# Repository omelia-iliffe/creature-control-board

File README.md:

# SECOND RELEASE COMING SOON
Open an issue to request features!

I am developing a circuit board for non-organic creatures.

#### Useful links:
Auto-Program circuit - https://arduino.stackexchange.com/questions/38012/major-difference-between-dtr-signal-and-rts-signal

| GPIO Determining the Boot Mode |           |          |               |
|--------------------------------|-----------|----------|---------------|
| Pin                            | Default   | Run Mode | Download Mode |
| IO0                            | Pull-up   | 1        | 0             |
| TXD0                           | Pull-up   | 1        | x             |
| IO2                            | Pull-down | x        | 0             |
| IO5                            | Pull-up   | 1        | x             |
(Table from https://www.sparkfun.com/news/2017)

Breakout Board for LSM6DS3 - https://github.com/sparkfun/LSM6DS3_Breakout
https://learn.sparkfun.com/tutorials/lsm6ds3-breakout-hookup-guide

Breakout Board for TPA2005D1 - https://github.com/sparkfun/Mono_Audio_Amp_Breakout-TPA2005D1
http://cdn.sparkfun.com/datasheets/BreakoutBoards/Mono%20Audio%20Amp%20TPA2005D1%20v10.pdf

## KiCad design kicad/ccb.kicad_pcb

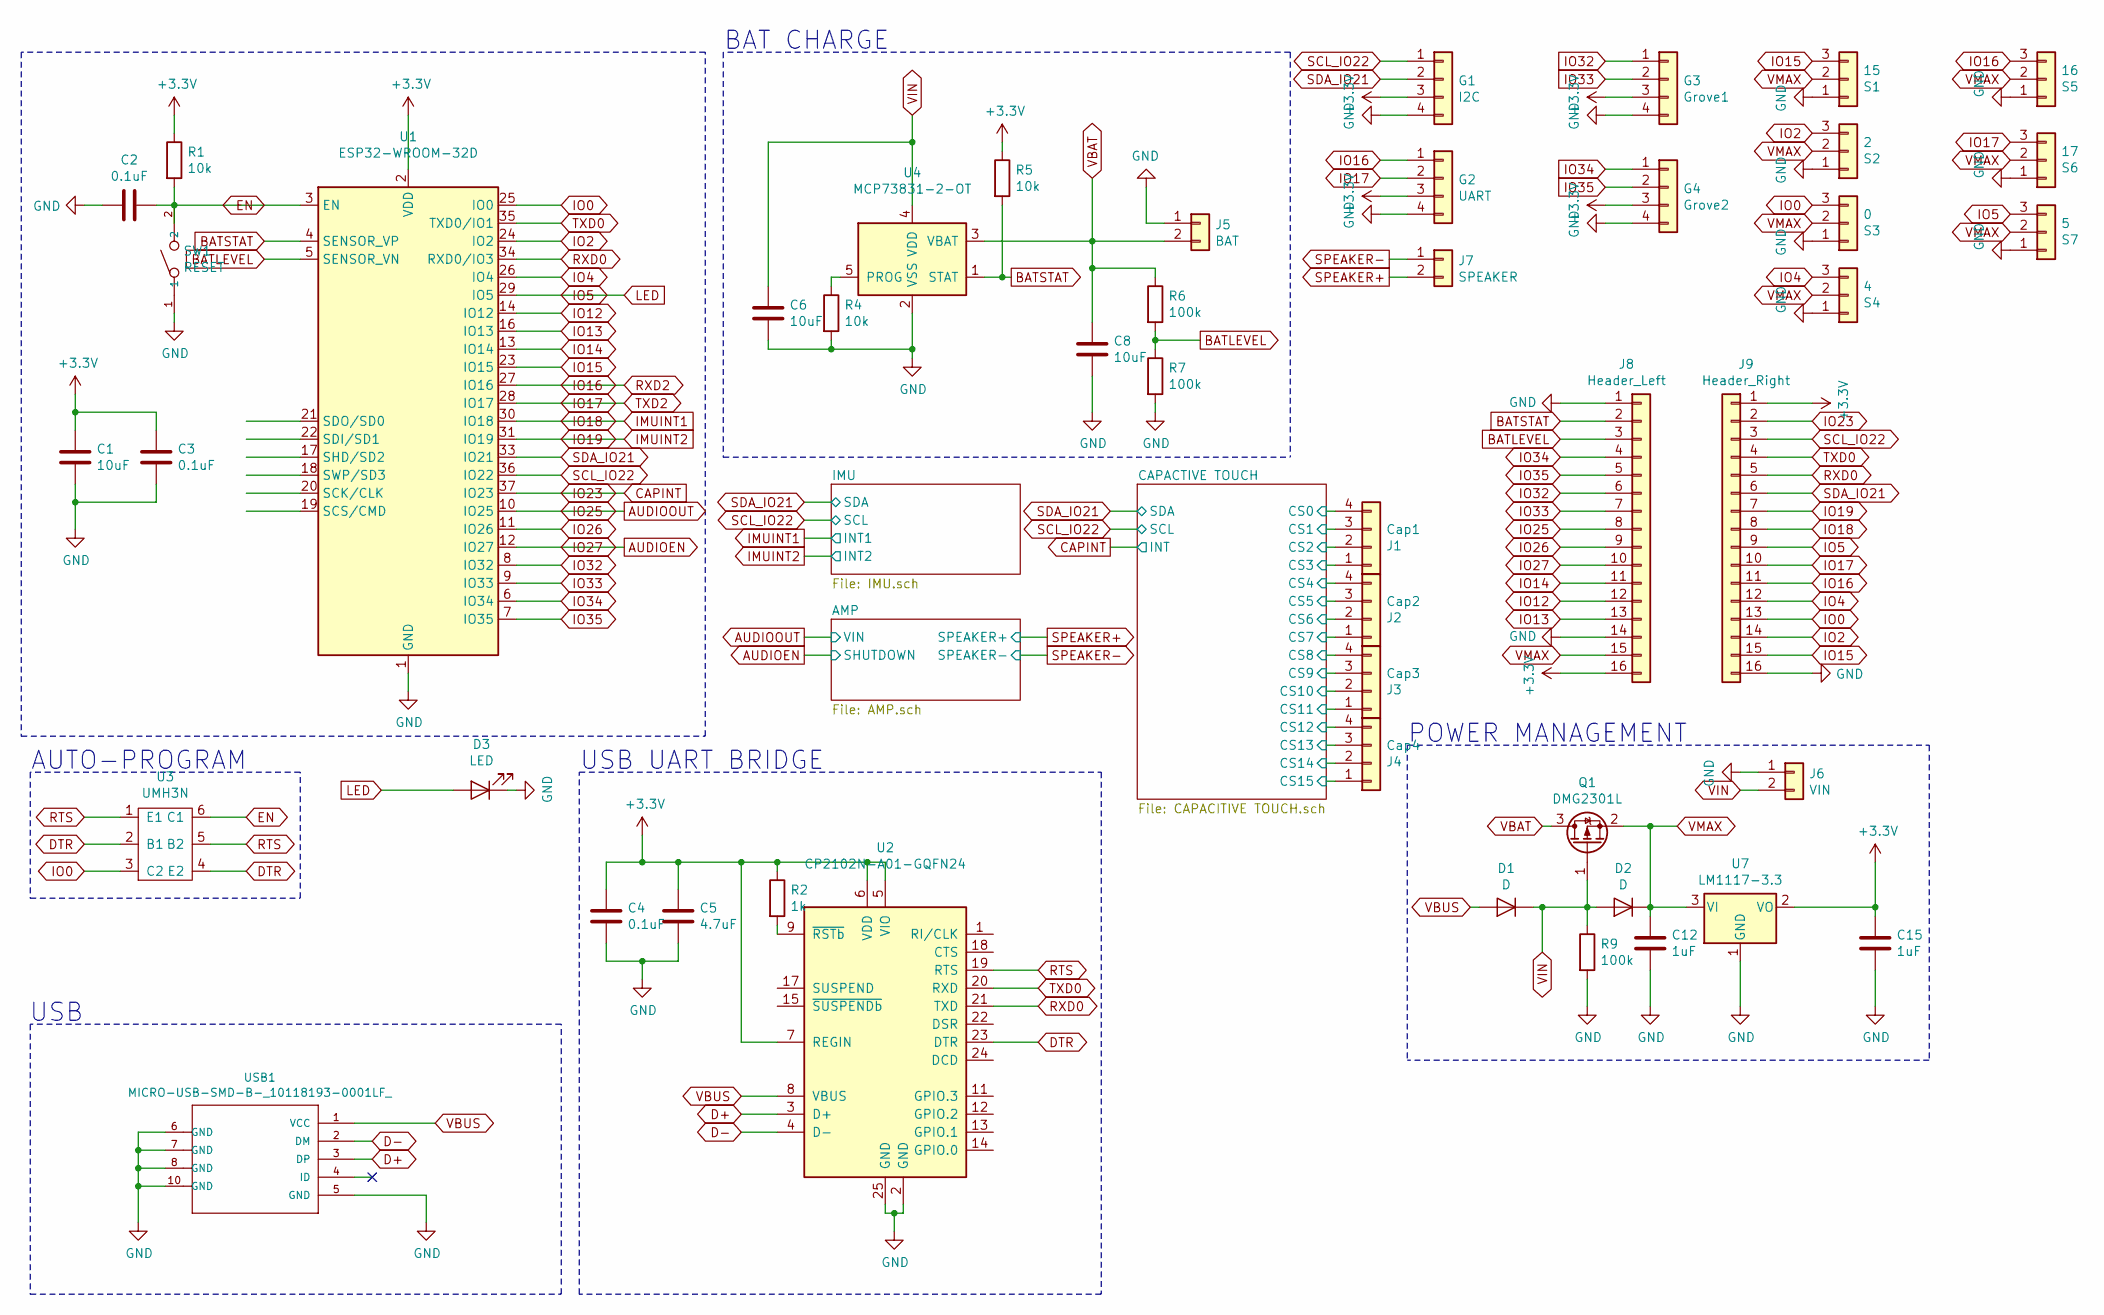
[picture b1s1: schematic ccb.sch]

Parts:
C1, C6, C8: 10uF; C_0805_2012Metric; MPN CL21A106KPFNNNE
C2, C3, C4: 0.1uF; C_0805_2012Metric; MPN CL21B104MACNNNC
C5: 4.7uF; C_0805_2012Metric; MPN CL21A475KPFNNNG
C12, C15: 1uF; C_0805_2012Metric; MPN CL21B105KOFNNNG
D1, D2: D; D_SOD-323; MPN BAT60JFILM
D3: LED; LED_1206_3216Metric_Pad1.42x1.75mm_HandSolder
G1: I2C; NS-Tech_Grove_1x04_P2mm_Vertical; MPN 110990030
G2: UART; NS-Tech_Grove_1x04_P2mm_Vertical; MPN 110990030
G3: Grove1; NS-Tech_Grove_1x04_P2mm_Vertical; MPN 110990030
G4: Grove2; NS-Tech_Grove_1x04_P2mm_Vertical; MPN 110990030
J1: Cap1; JST_PH_S4B-PH-K_1x04_P2.00mm_Horizontal; MPN S4B-PH-K-S(LF)(SN)
J2: Cap2; JST_PH_S4B-PH-K_1x04_P2.00mm_Horizontal; MPN S4B-PH-K-S(LF)(SN)
J3: Cap3; JST_PH_S4B-PH-K_1x04_P2.00mm_Horizontal; MPN S4B-PH-K-S(LF)(SN)
J4: Cap4; JST_PH_S4B-PH-K_1x04_P2.00mm_Horizontal; MPN S4B-PH-K-S(LF)(SN)
J5: BAT; JST_PH_S2B-PH-K_1x02_P2.00mm_Horizontal; MPN S2B-PH-K-S(LF)(SN)
J6: VIN; JST_PH_S2B-PH-K_1x02_P2.00mm_Horizontal; MPN S2B-PH-K-S(LF)(SN)
J7: SPEAKER; JST_PH_S2B-PH-K_1x02_P2.00mm_Horizontal; MPN S2B-PH-K-S(LF)(SN)
J8: Header_Left; PinSocket_1x16_P2.54mm_Vertical; MPN 0022032161
J9: Header_Right; PinSocket_1x16_P2.54mm_Vertical; MPN 0022032161
Q1: DMG2301L; SOT-23; MPN NTR3A052PZT1G
R1, R4, R5: 10k; R_0805_2012Metric; MPN RMCF0805FT10K0
R2: 1k; R_0805_2012Metric; MPN RMCF0805FT1K00
R6, R7, R9: 100k; R_0805_2012Metric; MPN RMCF0805FT100K
S1: 15; PinHeader_1x03_P2.54mm_Vertical; MPN WM4001-ND
S2: 2; PinHeader_1x03_P2.54mm_Vertical; MPN WM4001-ND
S3: 0; PinHeader_1x03_P2.54mm_Vertical; MPN WM4001-ND
S4: 4; PinHeader_1x03_P2.54mm_Vertical; MPN WM4001-ND
S5: 16; PinHeader_1x03_P2.54mm_Vertical; MPN WM4001-ND
S6: 17; PinHeader_1x03_P2.54mm_Vertical; MPN WM4001-ND
S7: 5; PinHeader_1x03_P2.54mm_Vertical; MPN WM4001-ND
SW1: RESET; SW2-2.6-3.0X2.5X1.2+0.4MM; MPN B3U-1000P
U1: ESP32-WROOM-32D; ESP32-WROOM-32; MPN ESP32-WROOM-32D
U2: CP2102N-A01-GQFN24; QFN-24-1EP_4x4mm_P0.5mm_EP2.6x2.6mm; MPN CP2102N-A02-GQFN24R
U3: UMH3N; MPN UMH3NTN
U4: MCP73831-2-OT; SOT-23-5; MPN MCP73831T-2ACI/OT
U7: LM1117-3.3; TO-252; MPN LM1117IMPX-3.3/NOPB
USB1: MICRO-USB-SMD-B-_10118193-0001LF_; MICRO-USB5+6P-SMD-0.65-B; MPN 10118193-0001LF

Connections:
+3V3: C1.2, C3.2, C4.2, C5.2, C15.2, G1.3, G2.3, G3.3, G4.3, J8.16, J9.1, R1.1, R2.1, R5.1, U1.2 (VDD), U2.5 (VIO), U2.6 (VDD), U2.7 (REGIN), U7.2 (VO); also elsewhere on the board
/CAPACTIVE TOUCH/CS0: J1.4; also elsewhere on the board
/CAPACTIVE TOUCH/CS1: J1.3; also elsewhere on the board
/CAPACTIVE TOUCH/CS2: J1.2; also elsewhere on the board
/CAPACTIVE TOUCH/CS3: J1.1; also elsewhere on the board
/CAPACTIVE TOUCH/CS4: J2.4; also elsewhere on the board
/CAPACTIVE TOUCH/CS5: J2.3; also elsewhere on the board
/CAPACTIVE TOUCH/CS6: J2.2; also elsewhere on the board
/CAPACTIVE TOUCH/CS7: J2.1; also elsewhere on the board
/CAPACTIVE TOUCH/CS8: J3.4; also elsewhere on the board
/CAPACTIVE TOUCH/CS9: J3.3; also elsewhere on the board
/CAPACTIVE TOUCH/CS10: J3.2; also elsewhere on the board
/CAPACTIVE TOUCH/CS11: J3.1; also elsewhere on the board
/CAPACTIVE TOUCH/CS12: J4.4; also elsewhere on the board
/CAPACTIVE TOUCH/CS13: J4.3; also elsewhere on the board
/CAPACTIVE TOUCH/CS14: J4.2; also elsewhere on the board
/CAPACTIVE TOUCH/CS15: J4.1; also elsewhere on the board
AUDIOEN: J8.10, U1.12 (IO27); also elsewhere on the board
AUDIOOUT: J8.8, U1.10 (IO25); also elsewhere on the board
BATLEVEL: J8.3, R6.2, R7.1, U1.5 (SENSOR_VN)
BATSTAT: J8.2, R5.2, U1.4 (SENSOR_VP), U4.1 (STAT)
CAPINT: J9.2, U1.37 (IO23); also elsewhere on the board
D+: U2.3 (D+), USB1.3 (DP)
D-: U2.4 (D-), USB1.2 (DM)
DTR: U2.23 (DTR), U3.2 (B1), U3.4 (E2)
EN: C2.1, R1.2, SW1.2, U1.3 (EN), U3.6 (C1)
GND: C1.1, C2.2, C3.1, C4.1, C5.1, C6.1, C8.1, C12.1, C15.1, D3.1 (K), G1.4, G2.4, G3.4, G4.4, J5.1, J6.1, J8.1, J8.14, J9.16, R4.2, R7.2, R9.2, S1.1, S2.1, S3.1, S4.1, S5.1, S6.1, S7.1, SW1.1, U1.1 (GND), U1.15 (GND), U1.38 (GND), U2.2 (GND), U2.25 (GND), U4.2 (VSS), U7.1 (GND), USB1.5 (GND), USB1.6 (GND), USB1.7 (GND), USB1.8 (GND), USB1.9 (GND), USB1.10 (GND), USB1.11 (GND); also elsewhere on the board
IMUINT1: J9.8, U1.30 (IO18); also elsewhere on the board
IMUINT2: J9.7, U1.31 (IO19); also elsewhere on the board
IO0: J9.13, S3.3, U1.25 (IO0), U3.3 (C2)
IO2: J9.14, S2.3, U1.24 (IO2)
IO4: J9.12, S4.3, U1.26 (IO4)
IO5: D3.2 (A), J9.9, S7.3, U1.29 (IO5)
IO12: J8.12, U1.14 (IO12)
IO13: J8.13, U1.16 (IO13)
IO14: J8.11, U1.13 (IO14)
IO15: J9.15, S1.3, U1.23 (IO15)
IO16: G2.1, J9.11, S5.3, U1.27 (IO16)
IO17: G2.2, J9.10, S6.3, U1.28 (IO17)
IO26: J8.9, U1.11 (IO26)
IO32: G3.1, J8.6, U1.8 (IO32)
IO33: G3.2, J8.7, U1.9 (IO33)
IO34: G4.1, J8.4, U1.6 (IO34)
IO35: G4.2, J8.5, U1.7 (IO35)
unnamed: R2.2, U2.9 (~RSTb)
unnamed: R4.1, U4.5 (PROG)
RTS: U2.19 (RTS), U3.1 (E1), U3.5 (B2)
RXD0: J9.5, U1.34 (RXD0/IO3), U2.21 (TXD)
SCL_IO22: G1.1, J9.3, U1.36 (IO22); also elsewhere on the board
SDA_IO21: G1.2, J9.6, U1.33 (IO21); also elsewhere on the board
SPEAKER+: J7.2; also elsewhere on the board
SPEAKER-: J7.1; also elsewhere on the board
TXD0: J9.4, U1.35 (TXD0/IO1), U2.20 (RXD)
VBAT: C8.2, J5.2, Q1.3 (D), R6.1, U4.3 (VBAT)
VBUS: D1.2 (A), U2.8 (VBUS), USB1.1 (VCC)
VIN: C6.2, D1.1 (K), D2.2 (A), J6.2, Q1.1 (G), R9.1, U4.4 (VDD)
VMAX: C12.2, D2.1 (K), J8.15, Q1.2 (S), S1.2, S2.2, S3.2, S4.2, S5.2, S6.2, S7.2, U7.3 (VI)

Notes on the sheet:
USB
USB UART BRIDGE
AUTO-PROGRAM
BAT CHARGE
POWER MANAGEMENT

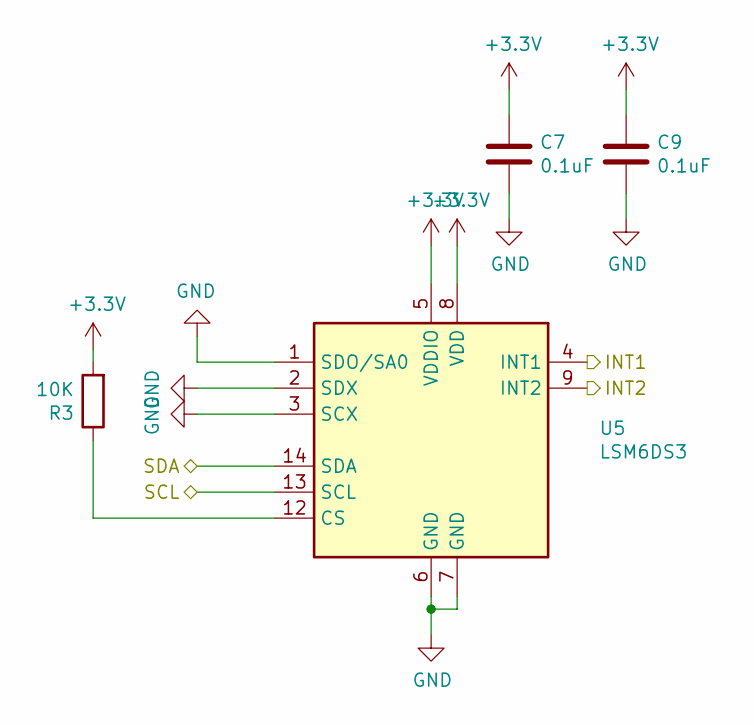
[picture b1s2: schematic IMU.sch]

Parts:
C7, C9: 0.1uF; C_0805_2012Metric; MPN CL21B104MACNNNC
R3: 10K; R_0805_2012Metric; MPN RMCF0805FT10K0
U5: LSM6DS3; LGA-14L_2.5x3mm__LSM6DS3; MPN LSM6DS3TR

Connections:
+3V3: C7.2, C9.2, R3.2, U5.5 (VDDIO), U5.8 (VDD); also elsewhere on the board
GND: C7.1, C9.1, U5.1 (SDO/SA0), U5.2 (SDX), U5.3 (SCX), U5.6 (GND), U5.7 (GND); also elsewhere on the board
IMUINT1: U5.4 (INT1); also elsewhere on the board
IMUINT2: U5.9 (INT2); also elsewhere on the board
unnamed: R3.1, U5.12 (CS)
SCL_IO22: U5.13 (SCL); also elsewhere on the board
SDA_IO21: U5.14 (SDA); also elsewhere on the board

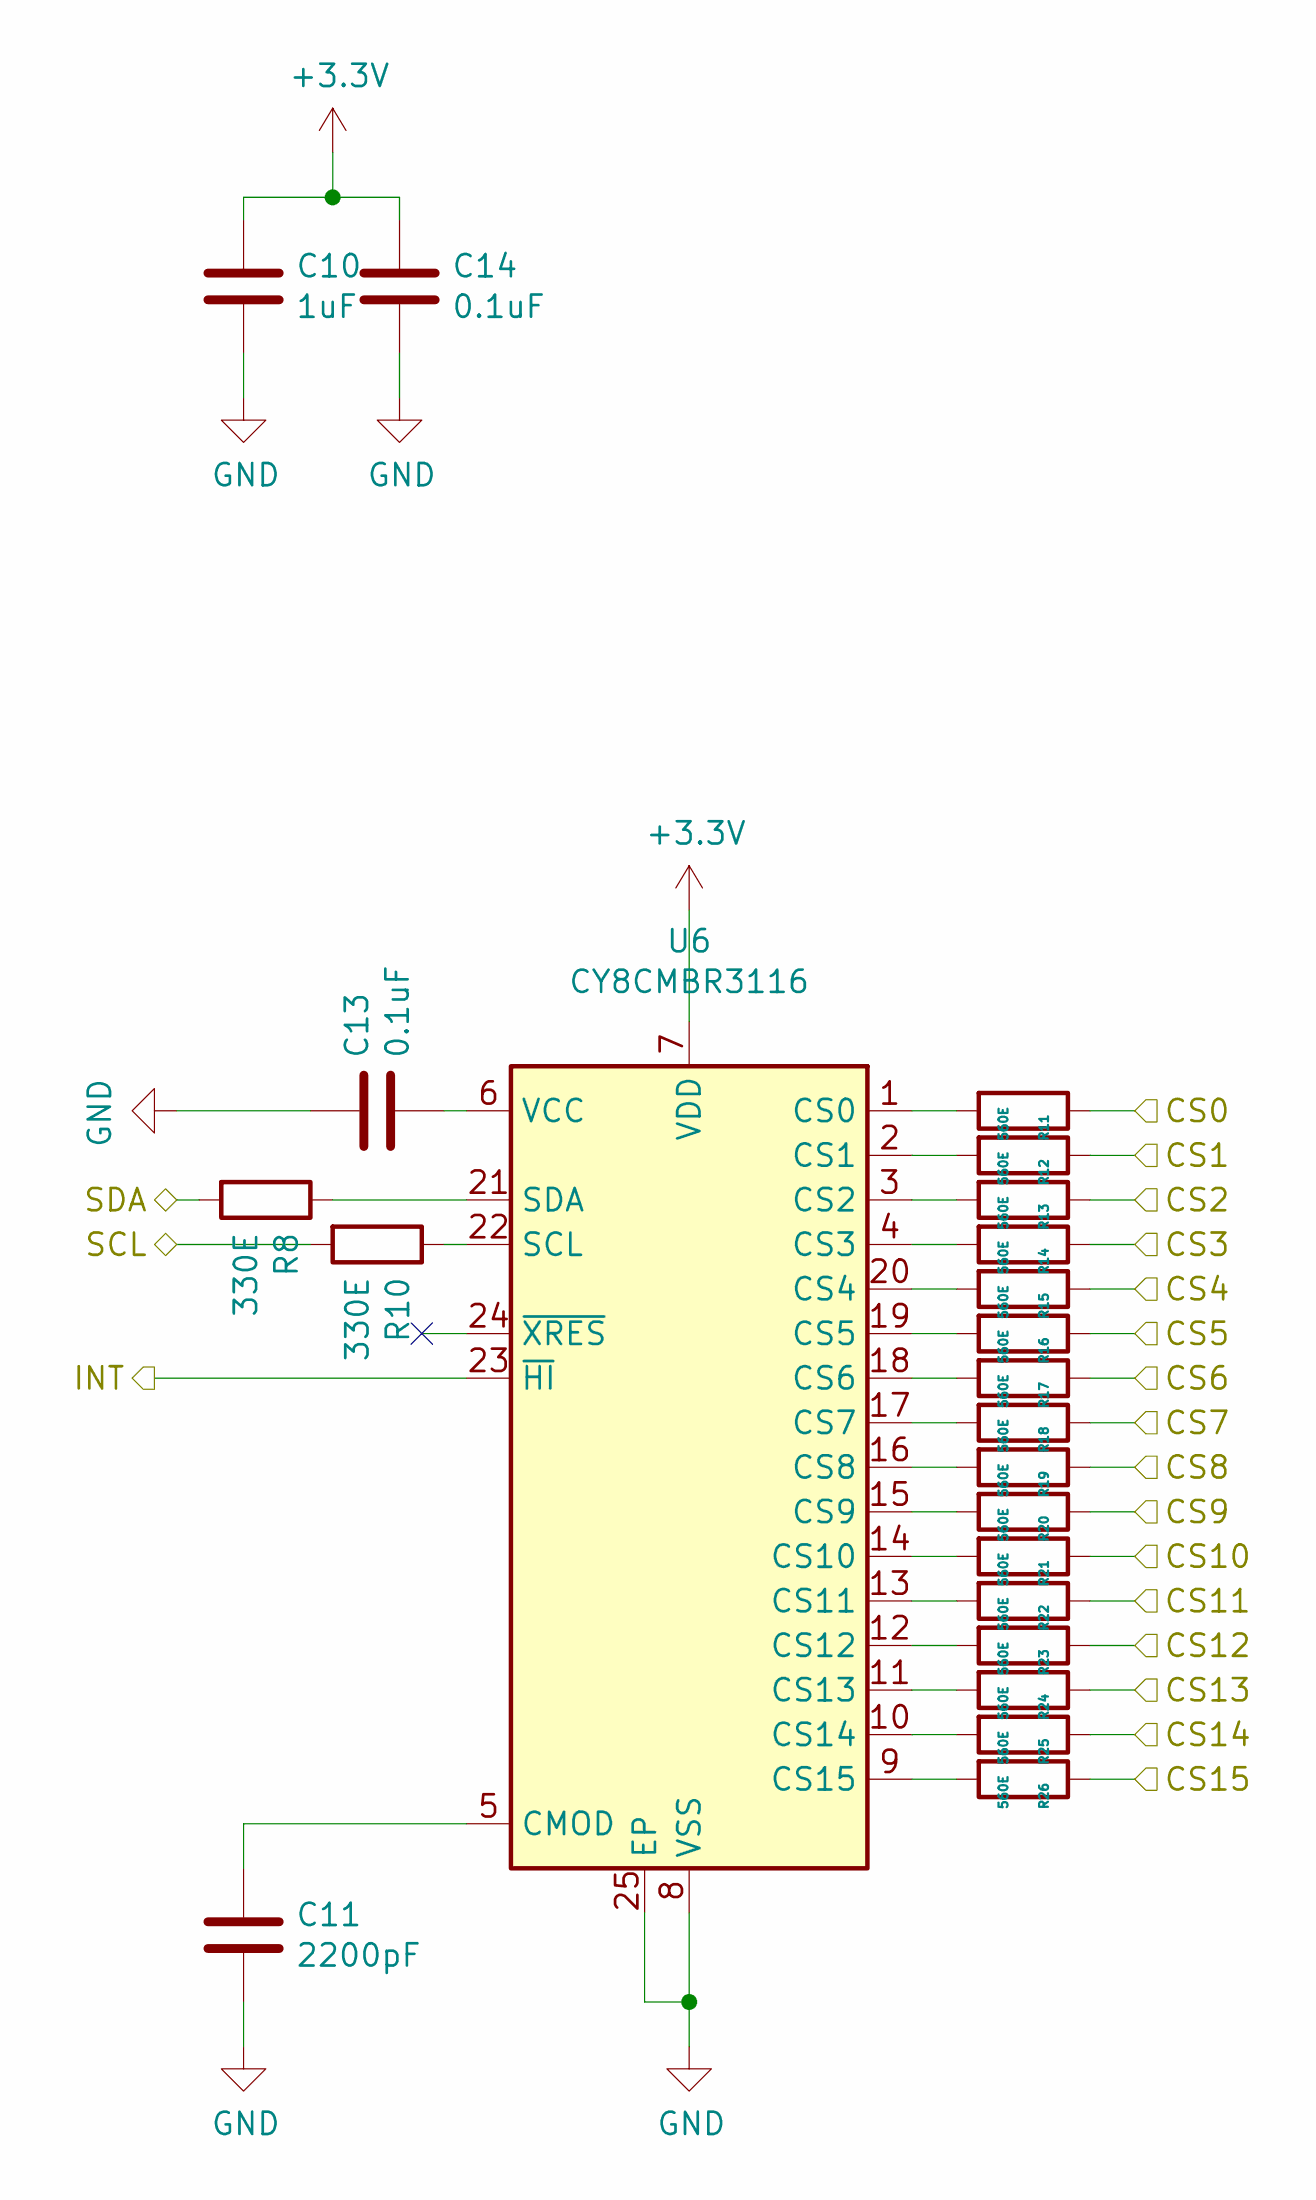
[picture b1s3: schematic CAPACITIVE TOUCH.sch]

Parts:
C10: 1uF; C_0805_2012Metric; MPN CL21B105KOFNNNG
C11: 2200pF; C_0805_2012Metric; MPN CL21B222JBANNNC
C13, C14: 0.1uF; C_0805_2012Metric; MPN CL21B104MACNNNC
R8, R10: 330E; R_0805_2012Metric; MPN RMCF0805FT330R
R11, R12, R13, R14, R15, R16, R17, R18, R19, R20, R21, R22, R23, R24, R25, R26: 560E; R_0805_2012Metric; MPN RMCF1206JG560R
U6: CY8CMBR3116; QFN-24-1EP_4x4mm_P0.5mm_EP2.6x2.6mm; MPN CY8CMBR3116

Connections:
+3V3: C10.2, C14.2, U6.7 (VDD); also elsewhere on the board
/CAPACTIVE TOUCH/CS0: R11.1; also elsewhere on the board
/CAPACTIVE TOUCH/CS1: R12.1; also elsewhere on the board
/CAPACTIVE TOUCH/CS2: R13.1; also elsewhere on the board
/CAPACTIVE TOUCH/CS3: R14.1; also elsewhere on the board
/CAPACTIVE TOUCH/CS4: R15.1; also elsewhere on the board
/CAPACTIVE TOUCH/CS5: R16.1; also elsewhere on the board
/CAPACTIVE TOUCH/CS6: R17.1; also elsewhere on the board
/CAPACTIVE TOUCH/CS7: R18.1; also elsewhere on the board
/CAPACTIVE TOUCH/CS8: R19.1; also elsewhere on the board
/CAPACTIVE TOUCH/CS9: R20.1; also elsewhere on the board
/CAPACTIVE TOUCH/CS10: R21.1; also elsewhere on the board
/CAPACTIVE TOUCH/CS11: R22.1; also elsewhere on the board
/CAPACTIVE TOUCH/CS12: R23.1; also elsewhere on the board
/CAPACTIVE TOUCH/CS13: R24.1; also elsewhere on the board
/CAPACTIVE TOUCH/CS14: R25.1; also elsewhere on the board
/CAPACTIVE TOUCH/CS15: R26.1; also elsewhere on the board
CAPINT: U6.23 (~HI); also elsewhere on the board
GND: C10.1, C11.1, C13.2, C14.1, U6.8 (VSS), U6.25 (EP); also elsewhere on the board
unnamed: C11.2, U6.5 (CMOD)
unnamed: C13.1, U6.6 (VCC)
unnamed: R8.1, U6.21 (SDA)
unnamed: R10.1, U6.22 (SCL)
unnamed: R11.2, U6.1 (CS0)
unnamed: R12.2, U6.2 (CS1)
unnamed: R13.2, U6.3 (CS2)
unnamed: R14.2, U6.4 (CS3)
unnamed: R15.2, U6.20 (CS4)
unnamed: R16.2, U6.19 (CS5)
unnamed: R17.2, U6.18 (CS6)
unnamed: R18.2, U6.17 (CS7)
unnamed: R19.2, U6.16 (CS8)
unnamed: R20.2, U6.15 (CS9)
unnamed: R21.2, U6.14 (CS10)
unnamed: R22.2, U6.13 (CS11)
unnamed: R23.2, U6.12 (CS12)
unnamed: R24.2, U6.11 (CS13)
unnamed: R25.2, U6.10 (CS14)
unnamed: R26.2, U6.9 (CS15)
SCL_IO22: R10.2; also elsewhere on the board
SDA_IO21: R8.2; also elsewhere on the board

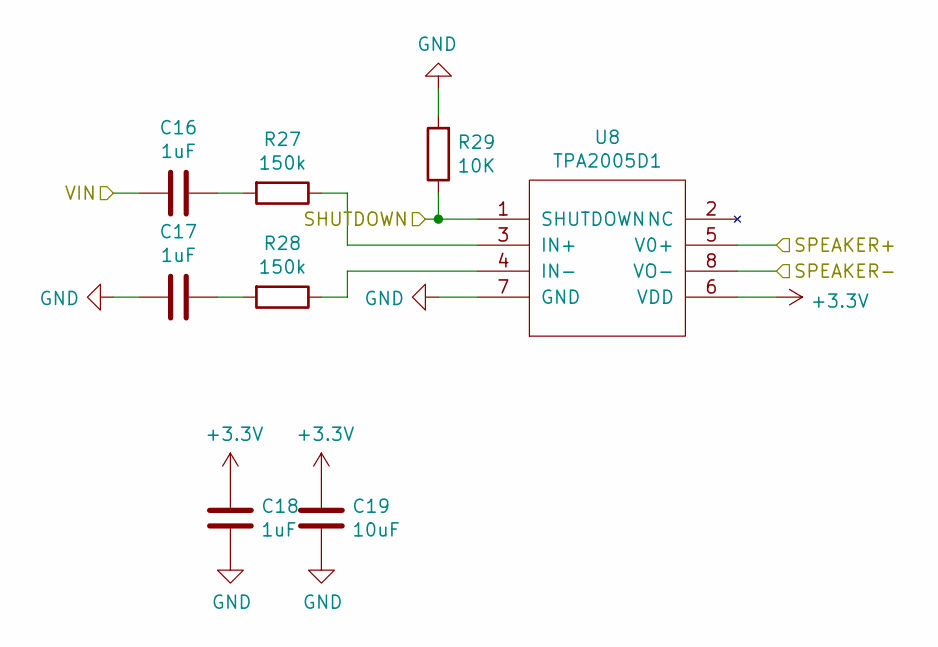
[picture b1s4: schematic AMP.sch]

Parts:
C16, C17, C18: 1uF; C_0805_2012Metric; MPN CL21B105KOFNNNG
C19: 10uF; C_0805_2012Metric; MPN CL21A106KPFNNNE
R27, R28: 150k; R_1206_3216Metric_Pad1.42x1.75mm_HandSolder; MPN RMCF1206FT150K
R29: 10K; R_0805_2012Metric; MPN RMCF0805FT10K0
U8: TPA2005D1; MPN TPA2005D1DGNR

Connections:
+3V3: C18.1, C19.1, U8.6 (VDD); also elsewhere on the board
AUDIOEN: R29.1, U8.1 (SHUTDOWN); also elsewhere on the board
AUDIOOUT: C16.1; also elsewhere on the board
GND: C17.1, C18.2, C19.2, R29.2, U8.7 (GND); also elsewhere on the board
unnamed: C16.2, R27.2
unnamed: C17.2, R28.2
unnamed: R27.1, U8.3 (IN+)
unnamed: R28.1, U8.4 (IN-)
SPEAKER+: U8.5 (V0+); also elsewhere on the board
SPEAKER-: U8.8 (VO-); also elsewhere on the board

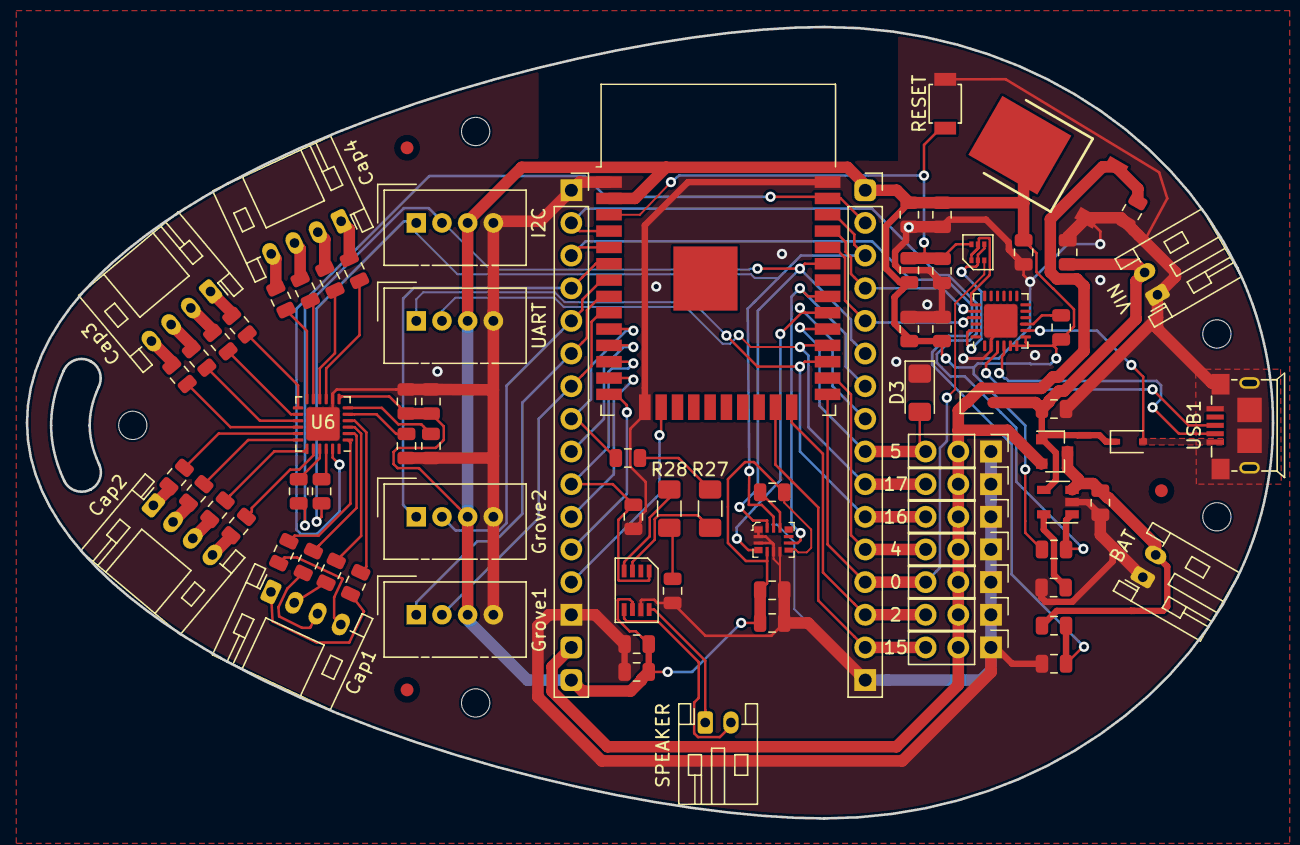
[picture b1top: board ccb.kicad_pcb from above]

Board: 2 copper layers, 96.9 x 61.6 mm, 82 parts (0 on the bottom side), 82 nets.

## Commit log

2019-07-26 inital commit
2019-07-26 completed esp32 basic layout
2019-07-27 added CY8CMBR3116, LSM6DS3
2019-08-09 completed inital layout
2019-08-11 updated bom
2019-08-11 updated gitignore
2019-08-11 moved libraries to folder
2019-08-15 laying out board
2019-08-18 completed layout (xh connectors)
2019-08-20 completed egg layout (final)
2019-08-23 added silkscreen, and manufacturing files
